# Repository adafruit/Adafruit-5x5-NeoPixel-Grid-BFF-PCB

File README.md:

## Adafruit 5x5 NeoPixel Grid BFF PCB

<a href="http://www.adafruit.com/products/5646"><br/>
Click here to purchase one from the Adafruit shop</a>

PCB files for the Adafruit 5x5 NeoPixel Grid BFF. 

Format is EagleCAD schematic and board layout
* https://www.adafruit.com/product/5646

### Description

Our QT Py boards are a great way to make very small microcontroller projects that pack a ton of power - and now we have a way for you to quickly add a glittering grid of 25 RGB addressable micro NeoPixels. It's an excellent way to make tiny wearable, cosplay, or IoT projects with dazzling LEDs.

We call this the Adafruit 5x5 NeoPixel Grid BFF - a "Best Friend Forever". When you were a kid you may have learned about the "buddy" system, well this product is kinda like that! A board that will watch your QT Py's back and act like a technicolor raincoat.

This PCB is designed to fit onto the back of any QT Py or Xiao board, it can be soldered into place or use pin and socket headers to make it removable. Onboard is a grid of 25 1.5x1.5mm NeoPixel LEDs (SK6805 to be exact), connected to pin A3 by default. You can cut/solder some jumpers to select A1, or A2 instead if you like. There's also solder pads for 5V, GND and IN data, in case you want to power externally. Advanced solderer's can use a thin wire to connect from the IN pad to other GPIO pins if desired.

We include some header that you can solder to your QT Py. You can also pick up an Itsy Bitsy short female header kit to make it removable but compact, you'll just need to trim down the headers to 7 pins long.

Comes as an assembled and tested PCB
For any QT Py or Xiao boards
Uses the 5V input via USB Type-C connector on QT Py to Power 25 NeoPixels
Default connected to pin A3 for NeoPixel data line. Not level shifted but the SK6805's are happy to run at 5V power with 3V input logic level.
QT Py is not included.

### License

Adafruit invests time and resources providing this open source design, please support Adafruit and open-source hardware by purchasing products from [Adafruit](https://www.adafruit.com)!

Designed by Limor Fried/Ladyada for Adafruit Industries.

Creative Commons Attribution/Share-Alike, all text above must be included in any redistribution. 
See license.txt for additional details.

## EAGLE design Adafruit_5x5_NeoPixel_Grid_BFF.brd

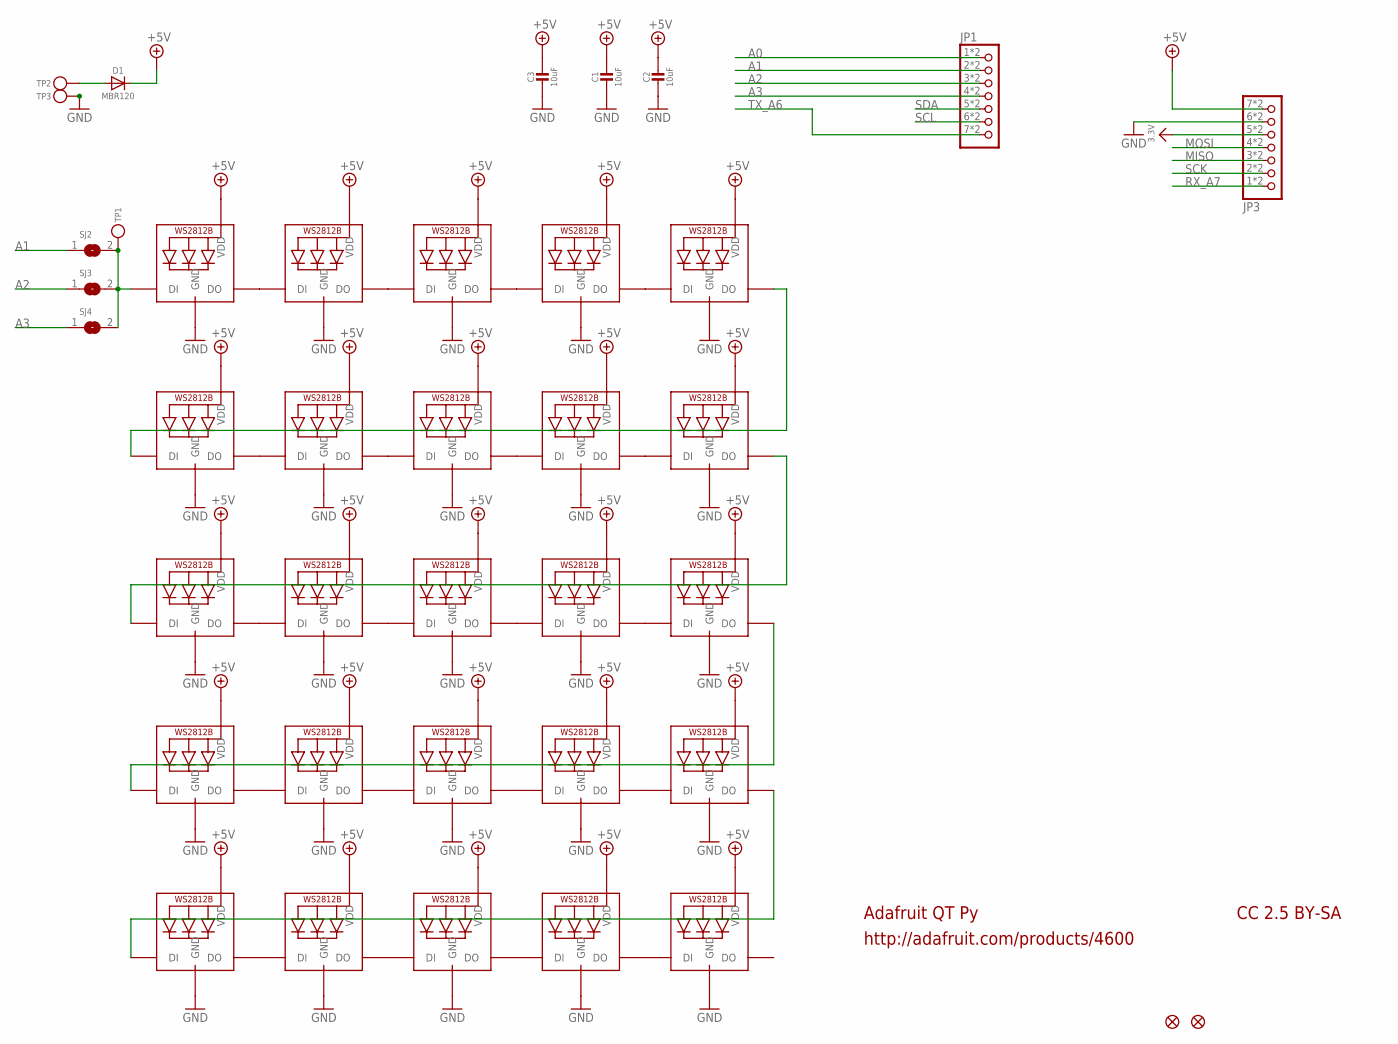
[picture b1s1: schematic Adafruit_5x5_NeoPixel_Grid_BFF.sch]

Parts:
C1, C2, C3: 10uF; 0603-NO
D1: MBR120; SOD-123
JP1, JP3: HEADER-1X7_CASTEL; 1X07_CASTEL
LED1, LED2, LED3, LED4, LED5, LED6, LED7, LED8, LED9, LED10, LED11, LED12, LED13, LED14, LED15, LED16, LED17, LED18, LED19, LED20, LED21, LED22, LED23, LED24, LED25: WS2812B_SK6805_1515; SK6805_1515
SJ2, SJ3: SOLDERJUMPER; SOLDERJUMPER_ARROW_NOPASTE
SJ4: SOLDERJUMPERCLOSED; SOLDERJUMPER_CLOSEDWIRE
TP1: TESTPOINT_1X3; TESTPOINT_RECT_1X3MM
TP2: TESTPOINT_PLUS13; TESTPOINT_PLUS_1X3MM
TP3: TESTPOINT_MINUS; TESTPOINT_MINUS_1X3MM
U$6, U$8: FIDUCIAL_1MM

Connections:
3.3V: JP3.5, JP3.5C (5)
+5V: C1.1, C2.1, C3.1, D1.C, JP3.7, JP3.7C (7), LED1.2 (VDD), LED2.2 (VDD), LED3.2 (VDD), LED4.2 (VDD), LED5.2 (VDD), LED6.2 (VDD), LED7.2 (VDD), LED8.2 (VDD), LED9.2 (VDD), LED10.2 (VDD), LED11.2 (VDD), LED12.2 (VDD), LED13.2 (VDD), LED14.2 (VDD), LED15.2 (VDD), LED16.2 (VDD), LED17.2 (VDD), LED18.2 (VDD), LED19.2 (VDD), LED20.2 (VDD), LED21.2 (VDD), LED22.2 (VDD), LED23.2 (VDD), LED24.2 (VDD), LED25.2 (VDD)
A0: JP1.1, JP1.1C (1)
A1: JP1.2, JP1.2C (2), SJ2.1
A2: JP1.3, JP1.3C (3), SJ3.1
A3: JP1.4, JP1.4C (4), SJ4.1
GND: C1.2, C2.2, C3.2, JP3.6, JP3.6C (6), LED1.4 (GND), LED2.4 (GND), LED3.4 (GND), LED4.4 (GND), LED5.4 (GND), LED6.4 (GND), LED7.4 (GND), LED8.4 (GND), LED9.4 (GND), LED10.4 (GND), LED11.4 (GND), LED12.4 (GND), LED13.4 (GND), LED14.4 (GND), LED15.4 (GND), LED16.4 (GND), LED17.4 (GND), LED18.4 (GND), LED19.4 (GND), LED20.4 (GND), LED21.4 (GND), LED22.4 (GND), LED23.4 (GND), LED24.4 (GND), LED25.4 (GND), TP3.P$1
MISO: JP3.3, JP3.3C (3)
MOSI: JP3.4, JP3.4C (4)
unnamed: LED1.3 (DO), LED2.1 (DI)
unnamed: LED2.3 (DO), LED3.1 (DI)
unnamed: LED3.3 (DO), LED4.1 (DI)
unnamed: LED4.3 (DO), LED5.1 (DI)
unnamed: LED6.3 (DO), LED7.1 (DI)
unnamed: LED7.3 (DO), LED8.1 (DI)
unnamed: LED8.3 (DO), LED9.1 (DI)
unnamed: LED9.3 (DO), LED10.1 (DI)
unnamed: LED11.3 (DO), LED12.1 (DI)
unnamed: LED12.3 (DO), LED13.1 (DI)
unnamed: LED13.3 (DO), LED14.1 (DI)
unnamed: LED14.3 (DO), LED15.1 (DI)
unnamed: LED16.3 (DO), LED17.1 (DI)
unnamed: LED17.3 (DO), LED18.1 (DI)
unnamed: LED18.3 (DO), LED19.1 (DI)
unnamed: LED19.3 (DO), LED20.1 (DI)
unnamed: LED21.3 (DO), LED22.1 (DI)
unnamed: LED22.3 (DO), LED23.1 (DI)
unnamed: LED23.3 (DO), LED24.1 (DI)
unnamed: LED24.3 (DO), LED25.1 (DI)
unnamed: LED5.3 (DO), LED6.1 (DI)
unnamed: LED10.3 (DO), LED11.1 (DI)
unnamed: LED15.3 (DO), LED16.1 (DI)
unnamed: LED20.3 (DO), LED21.1 (DI)
unnamed: LED1.1 (DI), SJ2.2, SJ3.2, SJ4.2, TP1.P$1
unnamed: D1.A, TP2.P$1
RX_A7: JP3.1, JP3.1C (1)
SCK: JP3.2, JP3.2C (2)
SCL: JP1.6, JP1.6C (6)
SDA: JP1.5, JP1.5C (5)
TX_A6: JP1.7, JP1.7C (7)

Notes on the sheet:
Adafruit QT Py
http://adafruit.com/products/4600
CC 2.5 BY-SA

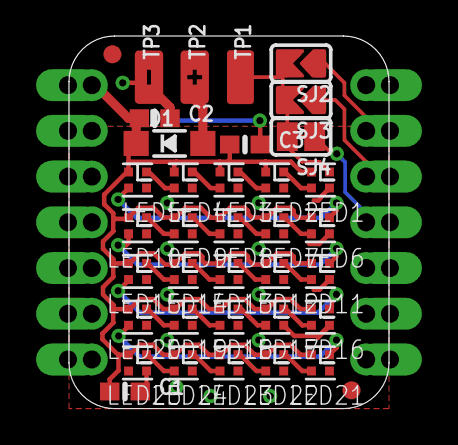
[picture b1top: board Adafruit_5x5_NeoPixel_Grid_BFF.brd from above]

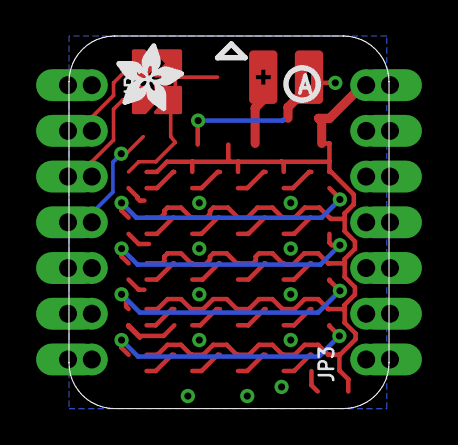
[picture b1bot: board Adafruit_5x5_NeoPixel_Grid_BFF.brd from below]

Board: 2 copper layers, 17.8 x 20.7 mm, 48 parts (6 on the bottom side), 40 nets.

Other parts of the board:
E$1: PCBFEAT-REV-040
E$3: ADAFRUIT_3.5MM
PLABEL0: PLABEL0
PLABEL2: PLABEL2
PLABEL3: PLABEL3
PLABEL4: PLABEL4
PLABEL5: PLABEL5
PLABEL7: PLABEL7
PLABEL8: PLABEL8

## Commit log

2022-11-22 adding cookiecutter output

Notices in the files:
parts and their libraries:
microbuilder: This work is placed in the public domain, and may be freely used for commercial and non-commercial work with the following conditions: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
